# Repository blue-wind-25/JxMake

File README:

====================================================================================================
JxMake
====================================================================================================

JxMake is a Java-based cross-platform build system primarily inspired by the syntax and features of
GNU Make, Perforce Jam, and CMake.

Additionally, JxMake supports several features not typically found in other console-based build
systems, including a simple built-in GUI, a serial console, a serial plotter, and integrated
programmers for some commonly used MCUs. The JxMake repository also includes hardware schematics
and PCB designs ranging from simple to moderately complex, covering generic GPIO, basic programmers,
and various tools.

Building JxMake requires Java SDK 8 or later (note that Java SDK 8 is an LTS version).

This project is mirrored on both SourceForge and GitHub:
    https://sourceforge.net/projects/jxmake
    https://github.com/blue-wind-25/JxMake

----------------------------------------------------------------------------------------------------

Please refer to the JxMake usage page (run it with the '-h' or '--browse-docs' option) for how to
use the program.

Please refer to 'docs/*.txt', 'test/*.jxm', and 'test/src/*/JxMakeFile' for the scripting language
syntax and examples.

----------------------------------------------------------------------------------------------------

All preprocessed '*.java' files that generated from their corresponding '*.java.in' files (and
optionally some '*.java.inc' files) are preprocessed using PCPP ('3rd_party/tools/pcpp/pcmd.py')
and GNU sed.

Currently, JxMake's loadable libraries (build scripts) are primarily focused on embedded systems
development. Future updates will enhance support for building desktop applications. However, please
note that these libraries are quite basic, so you may prefer to create custom libraries tailored
to your projects.

----------------------------------------------------------------------------------------------------
----------------------------------------------------------------------------------------------------
----------------------------------------------------------------------------------------------------

If you like this software (or part of this software), please consider donating to:
    PayPal: aloysius.indrayanto@gmail.com
to support the software development.

====================================================================================================

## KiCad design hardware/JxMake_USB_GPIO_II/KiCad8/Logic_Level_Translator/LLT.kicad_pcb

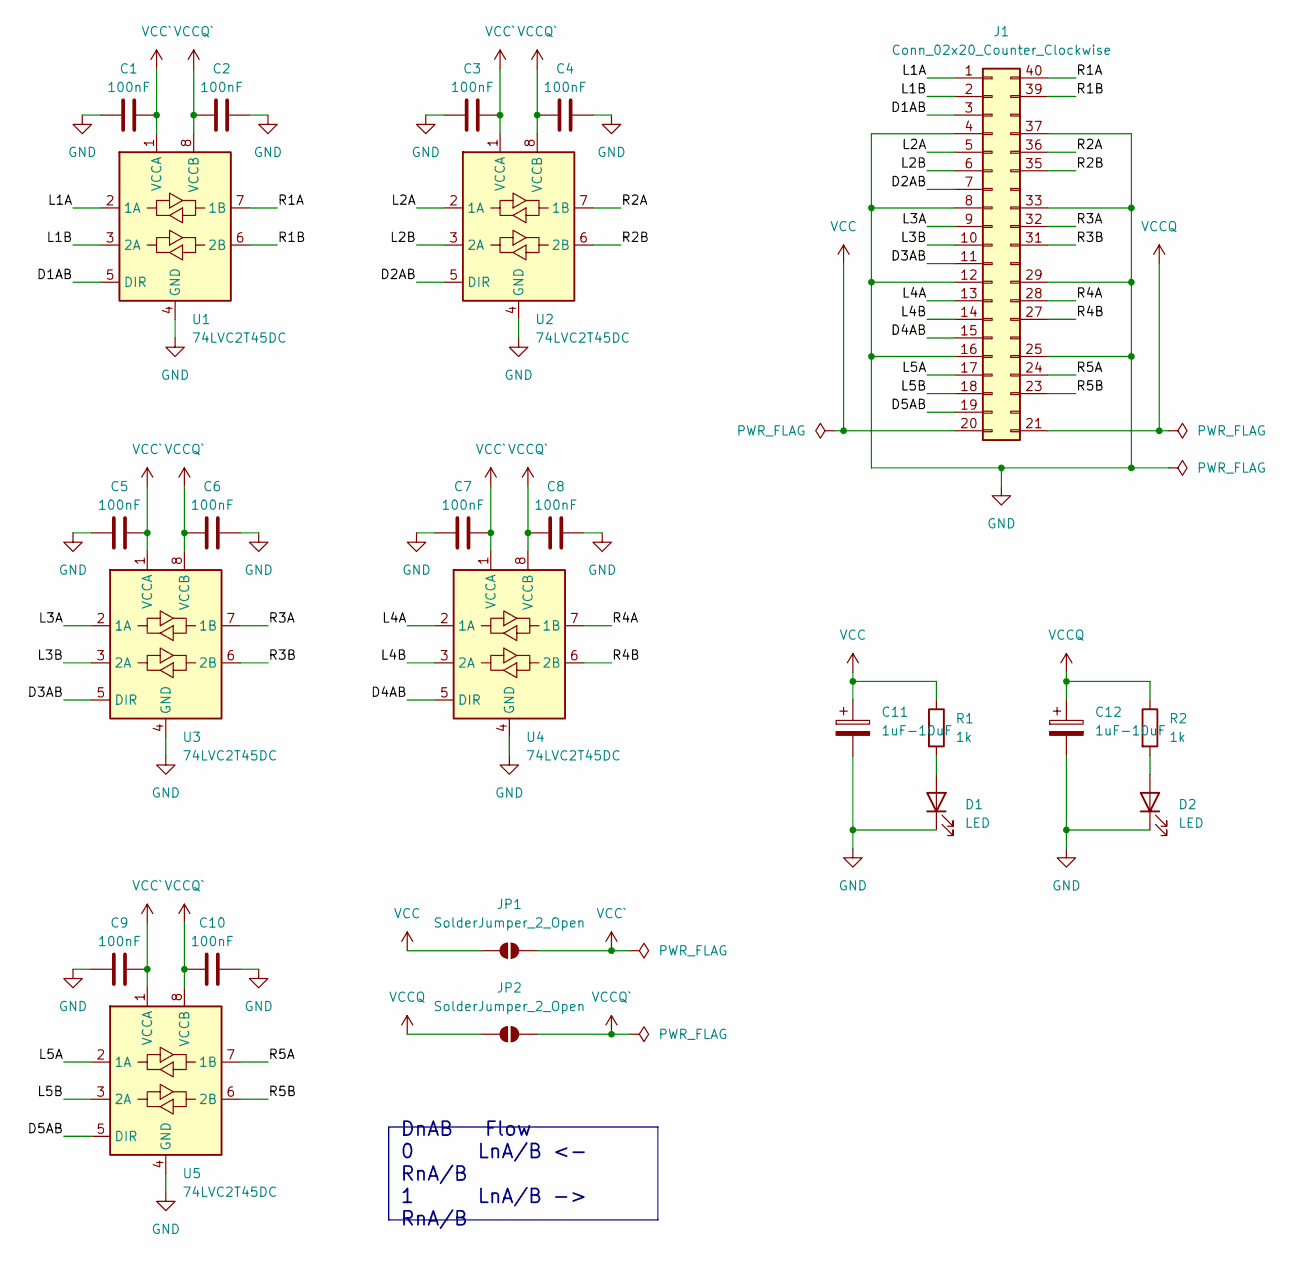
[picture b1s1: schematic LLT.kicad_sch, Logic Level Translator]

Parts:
C1, C2, C3, C4, C5, C6, C7, C8, C9, C10: 100nF; C_0805_2012Metric_Pad1.18x1.45mm_HandSolder
C11, C12: 1uF-10uF; CP_EIA-3216-12_Kemet-S_Pad1.58x1.35mm_HandSolder
D1, D2: LED; LED_0805_2012Metric_Pad1.15x1.40mm_HandSolder
J1: Conn_02x20_Counter_Clockwise; DIP-40_W25.4mm_LongPads
JP1, JP2: SolderJumper_2_Open; SolderJumper-2_P1.3mm_Open_Pad1.0x1.5mm
R1, R2: 1k; R_0805_2012Metric_Pad1.20x1.40mm_HandSolder
U1, U2, U3, U4, U5: 74LVC2T45DC; VSSOP-8_2.3x2mm_P0.5mm

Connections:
/D1AB: J1.3, U1.5 (DIR)
/D2AB: J1.7, U2.5 (DIR)
/D3AB: J1.11, U3.5 (DIR)
/D4AB: J1.15, U4.5 (DIR)
/D5AB: J1.19, U5.5 (DIR)
/L1A: J1.1, U1.2 (1A)
/L1B: J1.2, U1.3 (2A)
/L2A: J1.5, U2.2 (1A)
/L2B: J1.6, U2.3 (2A)
/L3A: J1.9, U3.2 (1A)
/L3B: J1.10, U3.3 (2A)
/L4A: J1.13, U4.2 (1A)
/L4B: J1.14, U4.3 (2A)
/L5A: J1.17, U5.2 (1A)
/L5B: J1.18, U5.3 (2A)
/R1A: J1.40, U1.7 (1B)
/R1B: J1.39, U1.6 (2B)
/R2A: J1.36, U2.7 (1B)
/R2B: J1.35, U2.6 (2B)
/R3A: J1.32, U3.7 (1B)
/R3B: J1.31, U3.6 (2B)
/R4A: J1.28, U4.7 (1B)
/R4B: J1.27, U4.6 (2B)
/R5A: J1.24, U5.7 (1B)
/R5B: J1.23, U5.6 (2B)
GND: C1.1, C2.2, C3.1, C4.2, C5.1, C6.2, C7.1, C8.2, C9.1, C10.2, C11.2, C12.2, D1.1 (K), D2.1 (K), J1.4, J1.8, J1.12, J1.16, J1.25, J1.29, J1.33, J1.37, U1.4 (GND), U2.4 (GND), U3.4 (GND), U4.4 (GND), U5.4 (GND)
unnamed: D1.2 (A), R1.2
unnamed: D2.2 (A), R2.2
VCC: C11.1, J1.20, JP1.1 (A), R1.1
VCCQ: C12.1, J1.21, JP2.1 (A), R2.1
VCCQ`: C2.1, C4.1, C6.1, C8.1, C10.1, JP2.2 (B), U1.8 (VCCB), U2.8 (VCCB), U3.8 (VCCB), U4.8 (VCCB), U5.8 (VCCB)
VCC`: C1.2, C3.2, C5.2, C7.2, C9.2, JP1.2 (B), U1.1 (VCCA), U2.1 (VCCA), U3.1 (VCCA), U4.1 (VCCA), U5.1 (VCCA)

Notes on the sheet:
DnAB Flow 0 LnA/B <- RnA/B 1 LnA/B -> RnA/B

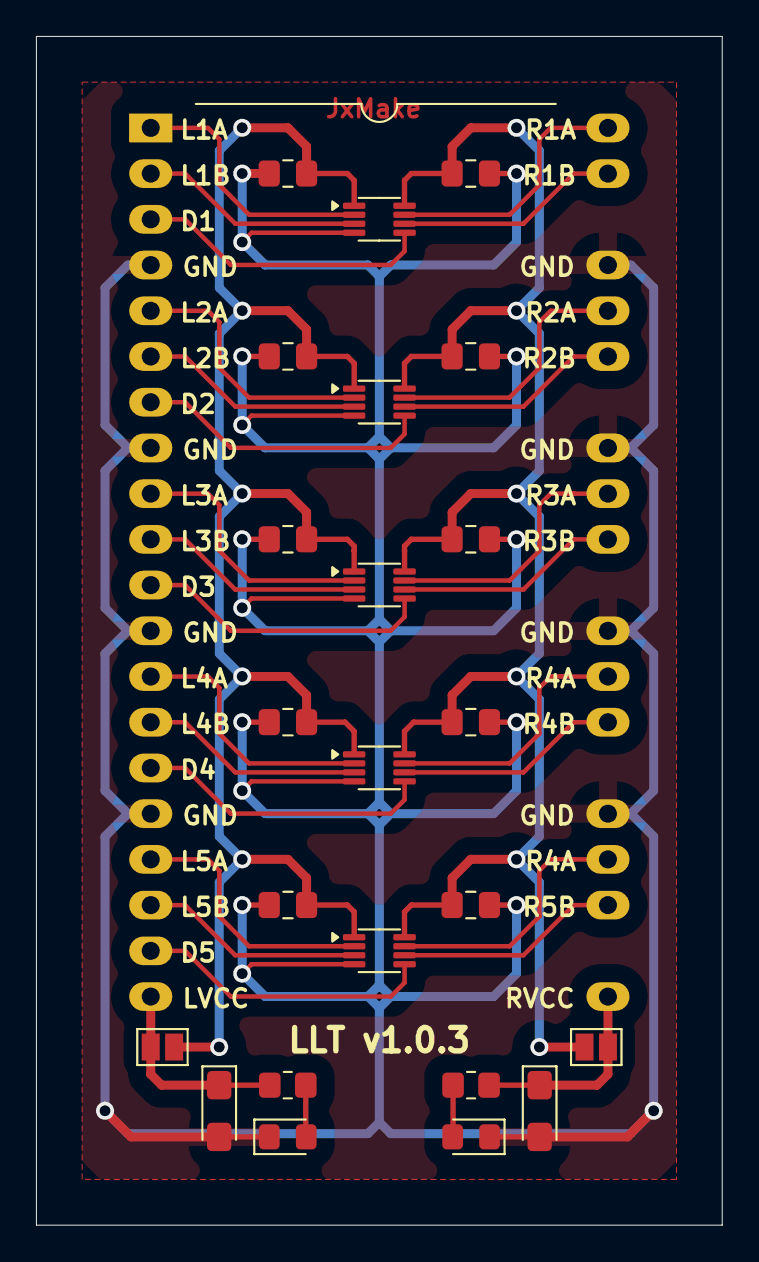
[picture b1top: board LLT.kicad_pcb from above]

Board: 2 copper layers, 38.1 x 66.0 mm, 24 parts (0 on the bottom side), 32 nets.

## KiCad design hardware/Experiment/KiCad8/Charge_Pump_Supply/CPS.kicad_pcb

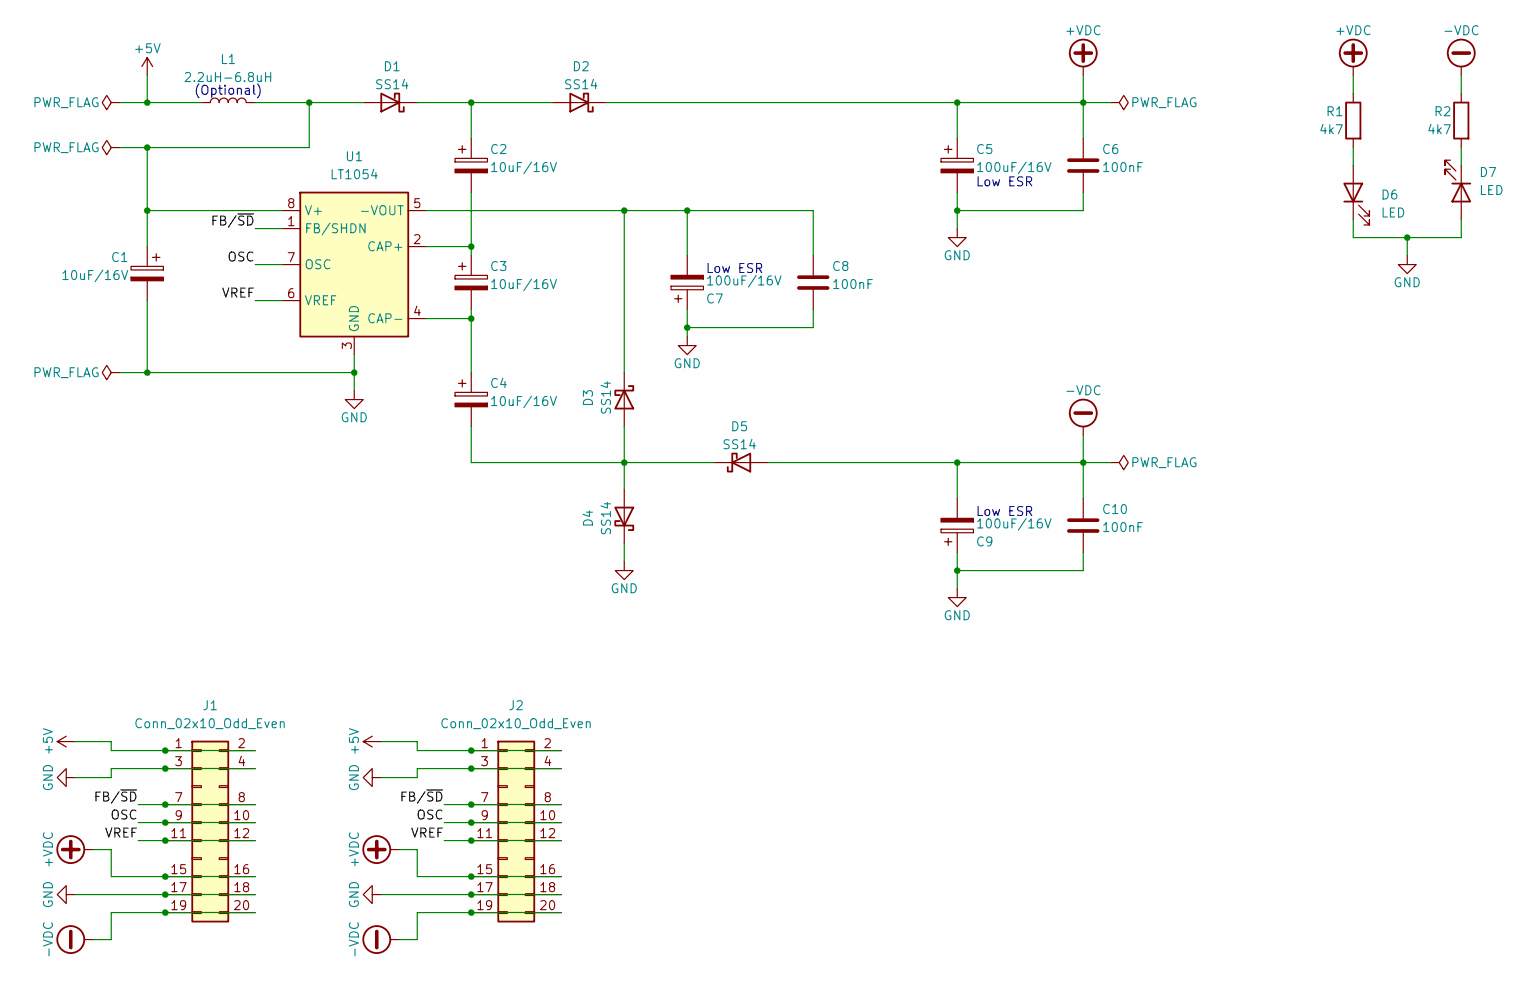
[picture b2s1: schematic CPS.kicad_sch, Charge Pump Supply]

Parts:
C1, C2, C3, C4: 10uF/16V; CP_EIA-3528-21_Kemet-B_Pad1.50x2.35mm_HandSolder
C5, C7, C9: 100uF/16V; CP_Elec_6.3x7.7
C6, C8, C10: 100nF; C_0805_2012Metric_Pad1.18x1.45mm_HandSolder
D1, D2, D3, D4, D5: SS14; D_SMA
D6, D7: LED; LED_0805_2012Metric_Pad1.15x1.40mm_HandSolder
J1, J2: Conn_02x10_Odd_Even; PinHeader_2x10_P2.54mm_Vertical
L1: 2.2uH-6.8uH; L_7.3x7.3_H4.5
R1, R2: 4k7; R_0805_2012Metric_Pad1.20x1.40mm_HandSolder
U1: LT1054; DIP-8_W7.62mm_LongPads

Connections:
+5V: J1.1, J1.2, J2.1, J2.2, L1.1
+VDC: C5.1, C6.1, D2.1 (K), J1.15, J1.16, J2.15, J2.16, R1.1
-VDC: C9.2, C10.1, D5.2 (A), J1.19, J1.20, J2.19, J2.20, R2.1
/FB/~SD: J1.7, J1.8, J2.7, J2.8, U1.1 (FB/SHDN)
/OSC: J1.9, J1.10, J2.9, J2.10, U1.7 (OSC)
/VREF: J1.11, J1.12, J2.11, J2.12, U1.6 (VREF)
GND: C1.2, C5.2, C6.2, C7.1, C8.2, C9.1, C10.2, D4.1 (K), D6.1 (K), D7.2 (A), J1.3, J1.4, J1.17, J1.18, J2.3, J2.4, J2.17, J2.18, U1.3 (GND)
unnamed: C1.1, D1.2 (A), L1.2, U1.8 (V+)
unnamed: C2.1, D1.1 (K), D2.2 (A)
unnamed: C4.2, D3.2 (A), D4.2 (A), D5.1 (K)
unnamed: C7.2, C8.1, D3.1 (K), U1.5 (-VOUT)
unnamed: D6.2 (A), R1.2
unnamed: D7.1 (K), R2.2
unnamed: C2.2, C3.1, U1.2 (CAP+)
unnamed: C3.2, C4.1, U1.4 (CAP-)

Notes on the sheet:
(Optional)
Low ESR

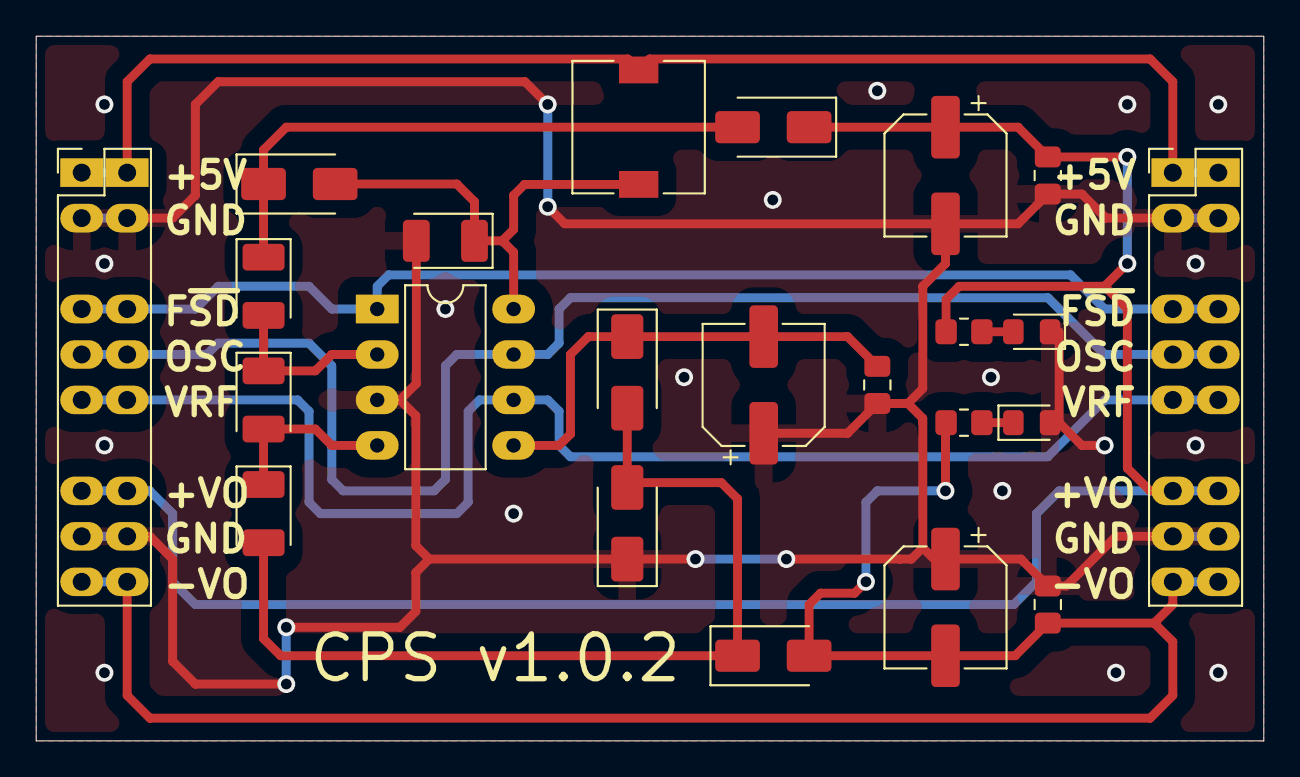
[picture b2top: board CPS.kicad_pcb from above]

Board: 2 copper layers, 68.6 x 39.4 mm, 23 parts (0 on the bottom side), 15 nets.

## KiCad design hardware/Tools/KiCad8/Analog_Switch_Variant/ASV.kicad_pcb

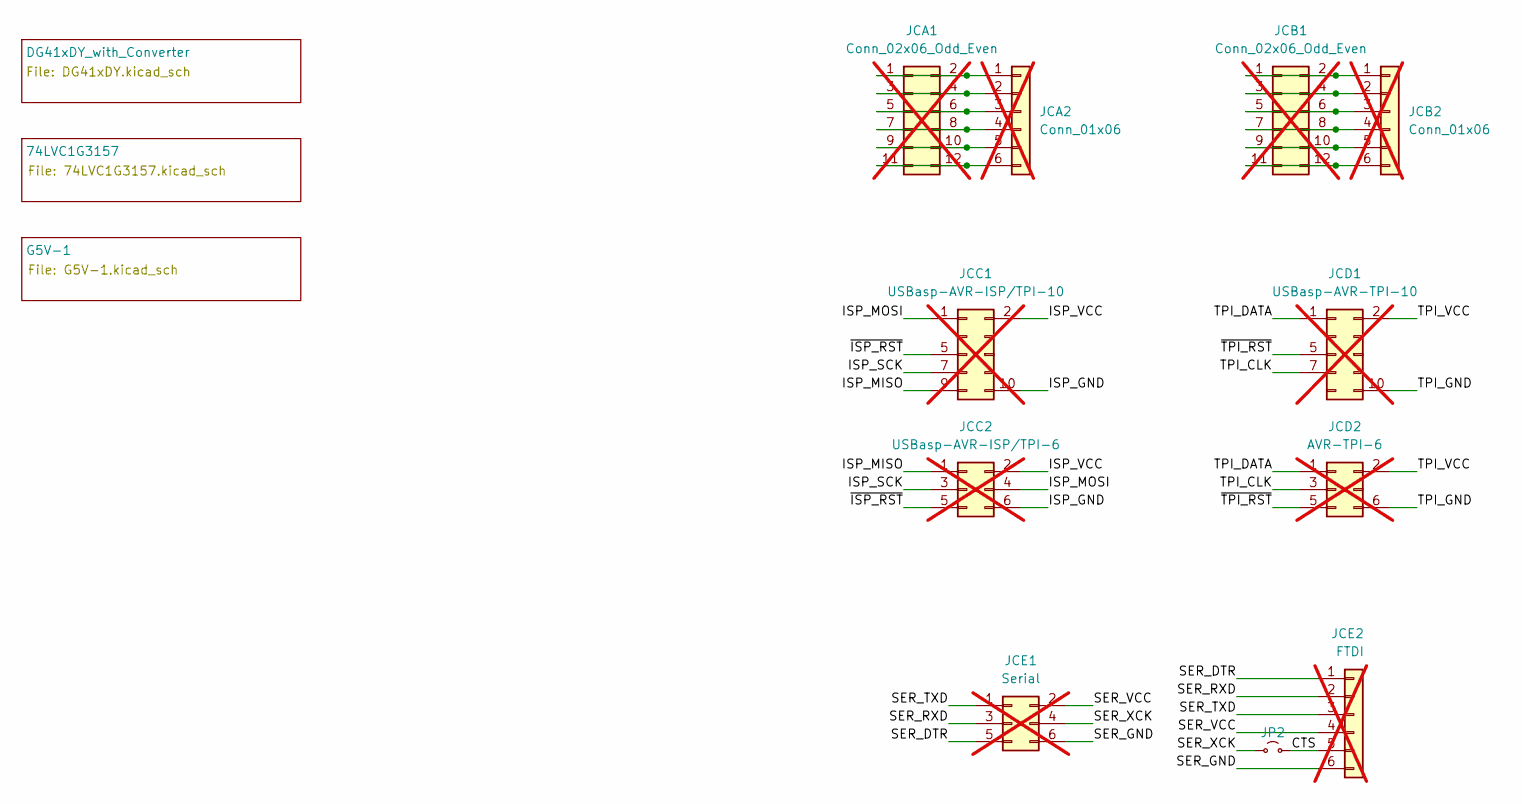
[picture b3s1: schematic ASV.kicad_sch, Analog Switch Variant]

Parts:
JCA1: Conn_02x06_Odd_Even; PinHeader_2x06_P2.54mm_Horizontal; not fitted
JCA2: Conn_01x06; PinHeader_1x06_P2.54mm_Horizontal; not fitted
JCB1: Conn_02x06_Odd_Even; PinHeader_2x06_P2.54mm_Horizontal; not fitted
JCB2: Conn_01x06; PinHeader_1x06_P2.54mm_Horizontal; not fitted
JCC1: USBasp-AVR-ISP/TPI-10; IDC-Header_2x05_P2.54mm_Vertical; not fitted
JCC2: USBasp-AVR-ISP/TPI-6; IDC-Header_2x03_P2.54mm_Vertical; not fitted
JCD1: USBasp-AVR-TPI-10; IDC-Header_2x05_P2.54mm_Vertical; not fitted
JCD2: AVR-TPI-6; IDC-Header_2x03_P2.54mm_Vertical; not fitted
JCE1: Serial; IDC-Header_2x03_P2.54mm_Vertical; not fitted
JCE2: FTDI; PinSocket_1x06_P2.54mm_Horizontal; not fitted
JP2: Jumper_2_Small_Open; SolderJumper-2_P1.3mm_Open_RoundedPad1.0x1.5mm

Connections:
/CTS: JCE2.5, JP2.2 (B)
/ISP_GND: JCC1.10, JCC2.6
/ISP_MISO: JCC1.9, JCC2.1
/ISP_MOSI: JCC1.1, JCC2.4
/ISP_SCK: JCC1.7, JCC2.3
/ISP_VCC: JCC1.2, JCC2.2
/SER_DTR: JCE1.5, JCE2.1
/SER_GND: JCE1.6, JCE2.6
/SER_RXD: JCE1.3, JCE2.2
/SER_TXD: JCE1.1, JCE2.3
/SER_VCC: JCE1.2, JCE2.4
/SER_XCK: JCE1.4, JP2.1 (A)
/TPI_CLK: JCD1.7, JCD2.3
/TPI_DATA: JCD1.1, JCD2.1
/TPI_GND: JCD1.10, JCD2.6
/TPI_VCC: JCD1.2, JCD2.2
/~ISP_RST: JCC1.5, JCC2.5
/~TPI_RST: JCD1.5, JCD2.5
unnamed: JCA1.1, JCA1.2, JCA2.1
unnamed: JCA1.3, JCA1.4, JCA2.2
unnamed: JCA1.5, JCA1.6, JCA2.3
unnamed: JCA1.7, JCA1.8, JCA2.4
unnamed: JCA1.9, JCA1.10, JCA2.5
unnamed: JCA1.11, JCA1.12, JCA2.6
unnamed: JCB1.1, JCB1.2, JCB2.1
unnamed: JCB1.3, JCB1.4, JCB2.2
unnamed: JCB1.5, JCB1.6, JCB2.3
unnamed: JCB1.7, JCB1.8, JCB2.4
unnamed: JCB1.9, JCB1.10, JCB2.5
unnamed: JCB1.11, JCB1.12, JCB2.6

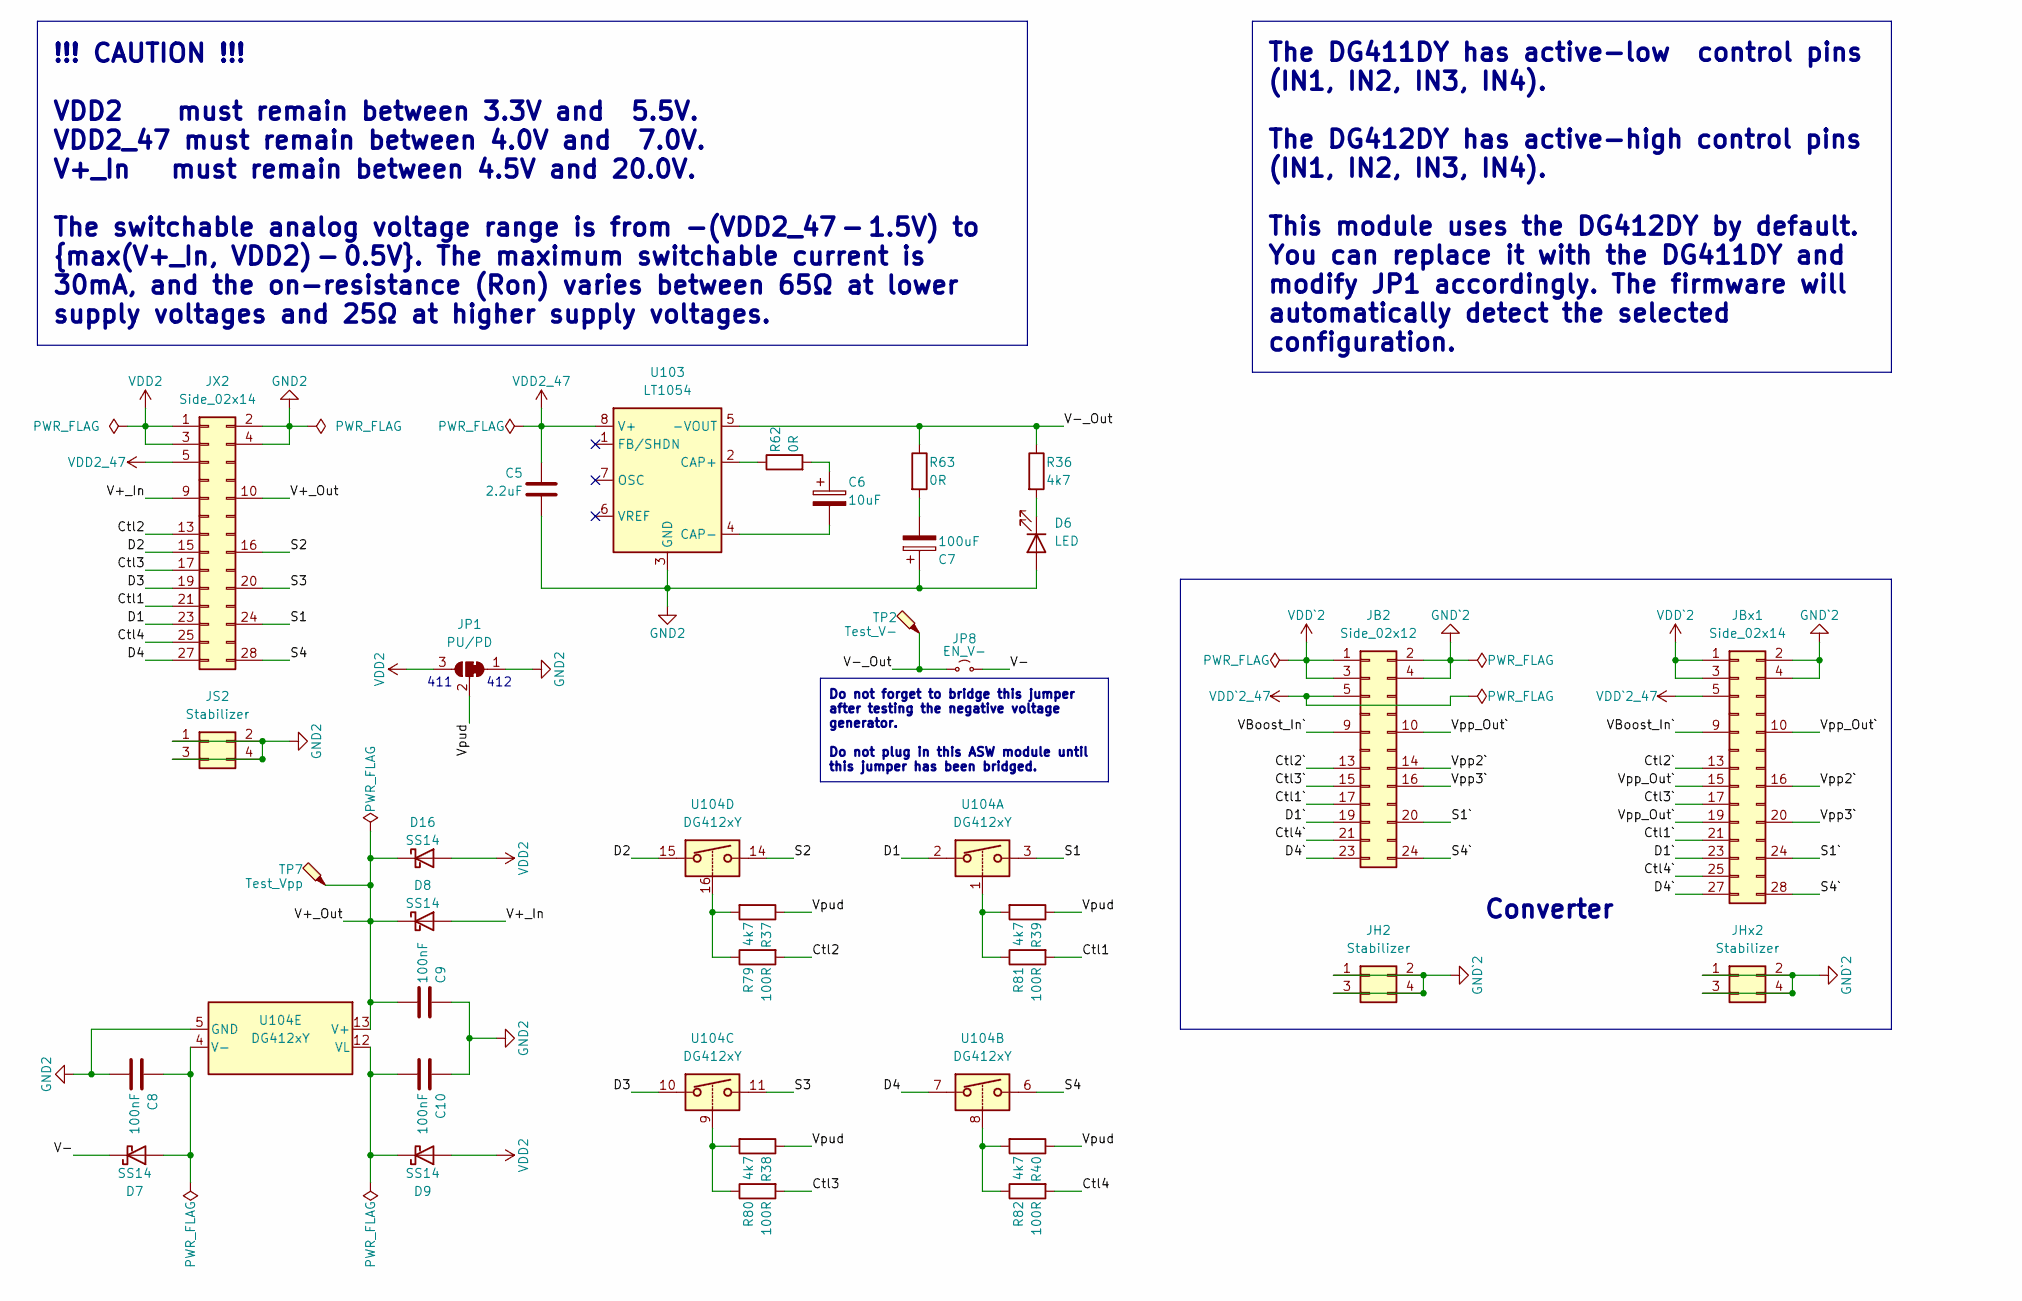
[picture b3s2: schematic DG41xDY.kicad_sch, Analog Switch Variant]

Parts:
C5: 2.2uF; C_0805_2012Metric_Pad1.18x1.45mm_HandSolder
C6: 10uF; CP_EIA-7360-38_Kemet-E_Pad2.25x4.25mm_HandSolder
C7: 100uF; CP_EIA-7360-38_Kemet-E_Pad2.25x4.25mm_HandSolder
C8, C9, C10: 100nF; C_0805_2012Metric_Pad1.18x1.45mm_HandSolder
D6: LED; LED_0805_2012Metric_Pad1.15x1.40mm_HandSolder
D7, D8, D9, D16: SS14; D_SMA
JB2: Side_02x12; PinHeader_2x12_P2.54mm_Vertical
JBx1: Side_02x14; PinHeader_2x14_P2.54mm_Vertical
JH2: Stabilizer; PinHeader_2x02_P2.54mm_Vertical
JHx2: Stabilizer; PinHeader_2x02_P2.54mm_Vertical
JP1: PU/PD; SolderJumper-3_P1.3mm_Bridged12_RoundedPad1.0x1.5mm
JP8: EN_V-; SolderJumper-2_P1.3mm_Open_RoundedPad1.0x1.5mm
JS2: Stabilizer; PinHeader_2x02_P2.54mm_Vertical
JX2: Side_02x14; PinHeader_2x14_P2.54mm_Vertical
R36, R37, R38, R39, R40: 4k7; R_0805_2012Metric_Pad1.20x1.40mm_HandSolder
R62, R63: 0R; R_0805_2012Metric_Pad1.20x1.40mm_HandSolder
R79, R80, R81, R82: 100R; R_0805_2012Metric_Pad1.20x1.40mm_HandSolder
TP2: Test_V-; TestPoint_THTPad_D1.5mm_Drill0.7mm
TP7: Test_Vpp; TestPoint_THTPad_D1.5mm_Drill0.7mm
U103: LT1054; DIP-8_W7.62mm_LongPads
U104: DG412xY; SOIC-16_3.9x9.9mm_P1.27mm

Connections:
/DG41xDY_with_Converter/Ctl1: JX2.21, R81.2
/DG41xDY_with_Converter/Ctl1`: JB2.17; also elsewhere on the board
/DG41xDY_with_Converter/Ctl2: JX2.13, R79.2
/DG41xDY_with_Converter/Ctl2`: JB2.13; also elsewhere on the board
/DG41xDY_with_Converter/Ctl3: JX2.17, R80.2
/DG41xDY_with_Converter/Ctl3`: JB2.15; also elsewhere on the board
/DG41xDY_with_Converter/Ctl4: JX2.25, R82.2
/DG41xDY_with_Converter/Ctl4`: JB2.21; also elsewhere on the board
/DG41xDY_with_Converter/D1: JX2.23, U104.2
/DG41xDY_with_Converter/D1`: JB2.19; also elsewhere on the board
/DG41xDY_with_Converter/D2: JX2.15, U104.15
/DG41xDY_with_Converter/D3: JX2.19, U104.10
/DG41xDY_with_Converter/D4: JX2.27, U104.7
/DG41xDY_with_Converter/D4`: JB2.23; also elsewhere on the board
/DG41xDY_with_Converter/S1: JX2.24, U104.3
/DG41xDY_with_Converter/S1`: JB2.20; also elsewhere on the board
/DG41xDY_with_Converter/S2: JX2.16, U104.14
/DG41xDY_with_Converter/S3: JX2.20, U104.11
/DG41xDY_with_Converter/S4: JX2.28, U104.6
/DG41xDY_with_Converter/S4`: JB2.24; also elsewhere on the board
/DG41xDY_with_Converter/V+_In: D8.2 (A), JX2.9
/DG41xDY_with_Converter/V+_Out: C9.2, D8.1 (K), D16.1 (K), JX2.10, TP7.1, U104.13 (V+)
/DG41xDY_with_Converter/V-: D7.1 (K), JP8.2 (B)
/DG41xDY_with_Converter/V-_Out: JP8.1 (A), R36.1, R63.1, TP2.1, U103.5 (-VOUT)
/DG41xDY_with_Converter/VBoost_In`: JB2.9; also elsewhere on the board
/DG41xDY_with_Converter/Vpp2`: JB2.14; also elsewhere on the board
/DG41xDY_with_Converter/Vpp3`: JB2.16; also elsewhere on the board
/DG41xDY_with_Converter/Vpp_Out`: JB2.10; also elsewhere on the board
/DG41xDY_with_Converter/Vpud: JP1.2 (C), R37.1, R38.1, R39.1, R40.1
GND2: C5.2, C7.1, C8.2, C9.1, C10.1, D6.2 (A), JP1.1 (A), JS2.1, JS2.2, JS2.3, JS2.4, JX2.2, JX2.4, U103.3 (GND), U104.5 (GND)
GND`2: JB2.2, JB2.4, JH2.1, JH2.2, JH2.3, JH2.4, JHx2.1, JHx2.2, JHx2.3, JHx2.4; also elsewhere on the board
unnamed: C6.1, R62.2
unnamed: C7.2, R63.2
unnamed: D6.1 (K), R36.2
unnamed: C8.1, D7.2 (A), U104.4 (V-)
unnamed: C10.2, D9.1 (K), U104.12 (VL)
unnamed: R37.2, R79.1, U104.16
unnamed: R38.2, R80.1, U104.9
unnamed: R39.2, R81.1, U104.1
unnamed: R40.2, R82.1, U104.8
unnamed: R62.1, U103.2 (CAP+)
unnamed: C6.2, U103.4 (CAP-)
VDD2: D9.2 (A), D16.2 (A), JP1.3 (B), JX2.1, JX2.3
VDD2_47: C5.1, JX2.5, U103.8 (V+)
VDD`2: JB2.1, JB2.3; also elsewhere on the board
VDD`2_47: JB2.5; also elsewhere on the board

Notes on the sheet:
Do not forget to bridge this jumper after testing the negative voltage generator. Do not plug in this ASW module until this jumper has been bridged.
The DG411DY has active-low control pins (IN1, IN2, IN3, IN4). The DG412DY has active-high control pins (IN1, IN2, IN3, IN4). This module uses the DG412DY by default. You can replace it with the DG411DY and modify JP1 accordingly. The firmware will automatically detect the selected configuration.
!!! CAUTION !!! VDD2 must remain between 3.3V and 5.5V. VDD2_47 must remain between 4.0V and 7.0V. V+_In must remain between 4.5V and 20.0V. The switchable analog voltage range is from -(VDD2_47 - 1.5V) to {max(V+_In, VDD2) - 0.5V}. The maximum switchable current is 30mA, and the on-resistance (Ron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
Converter
411
412

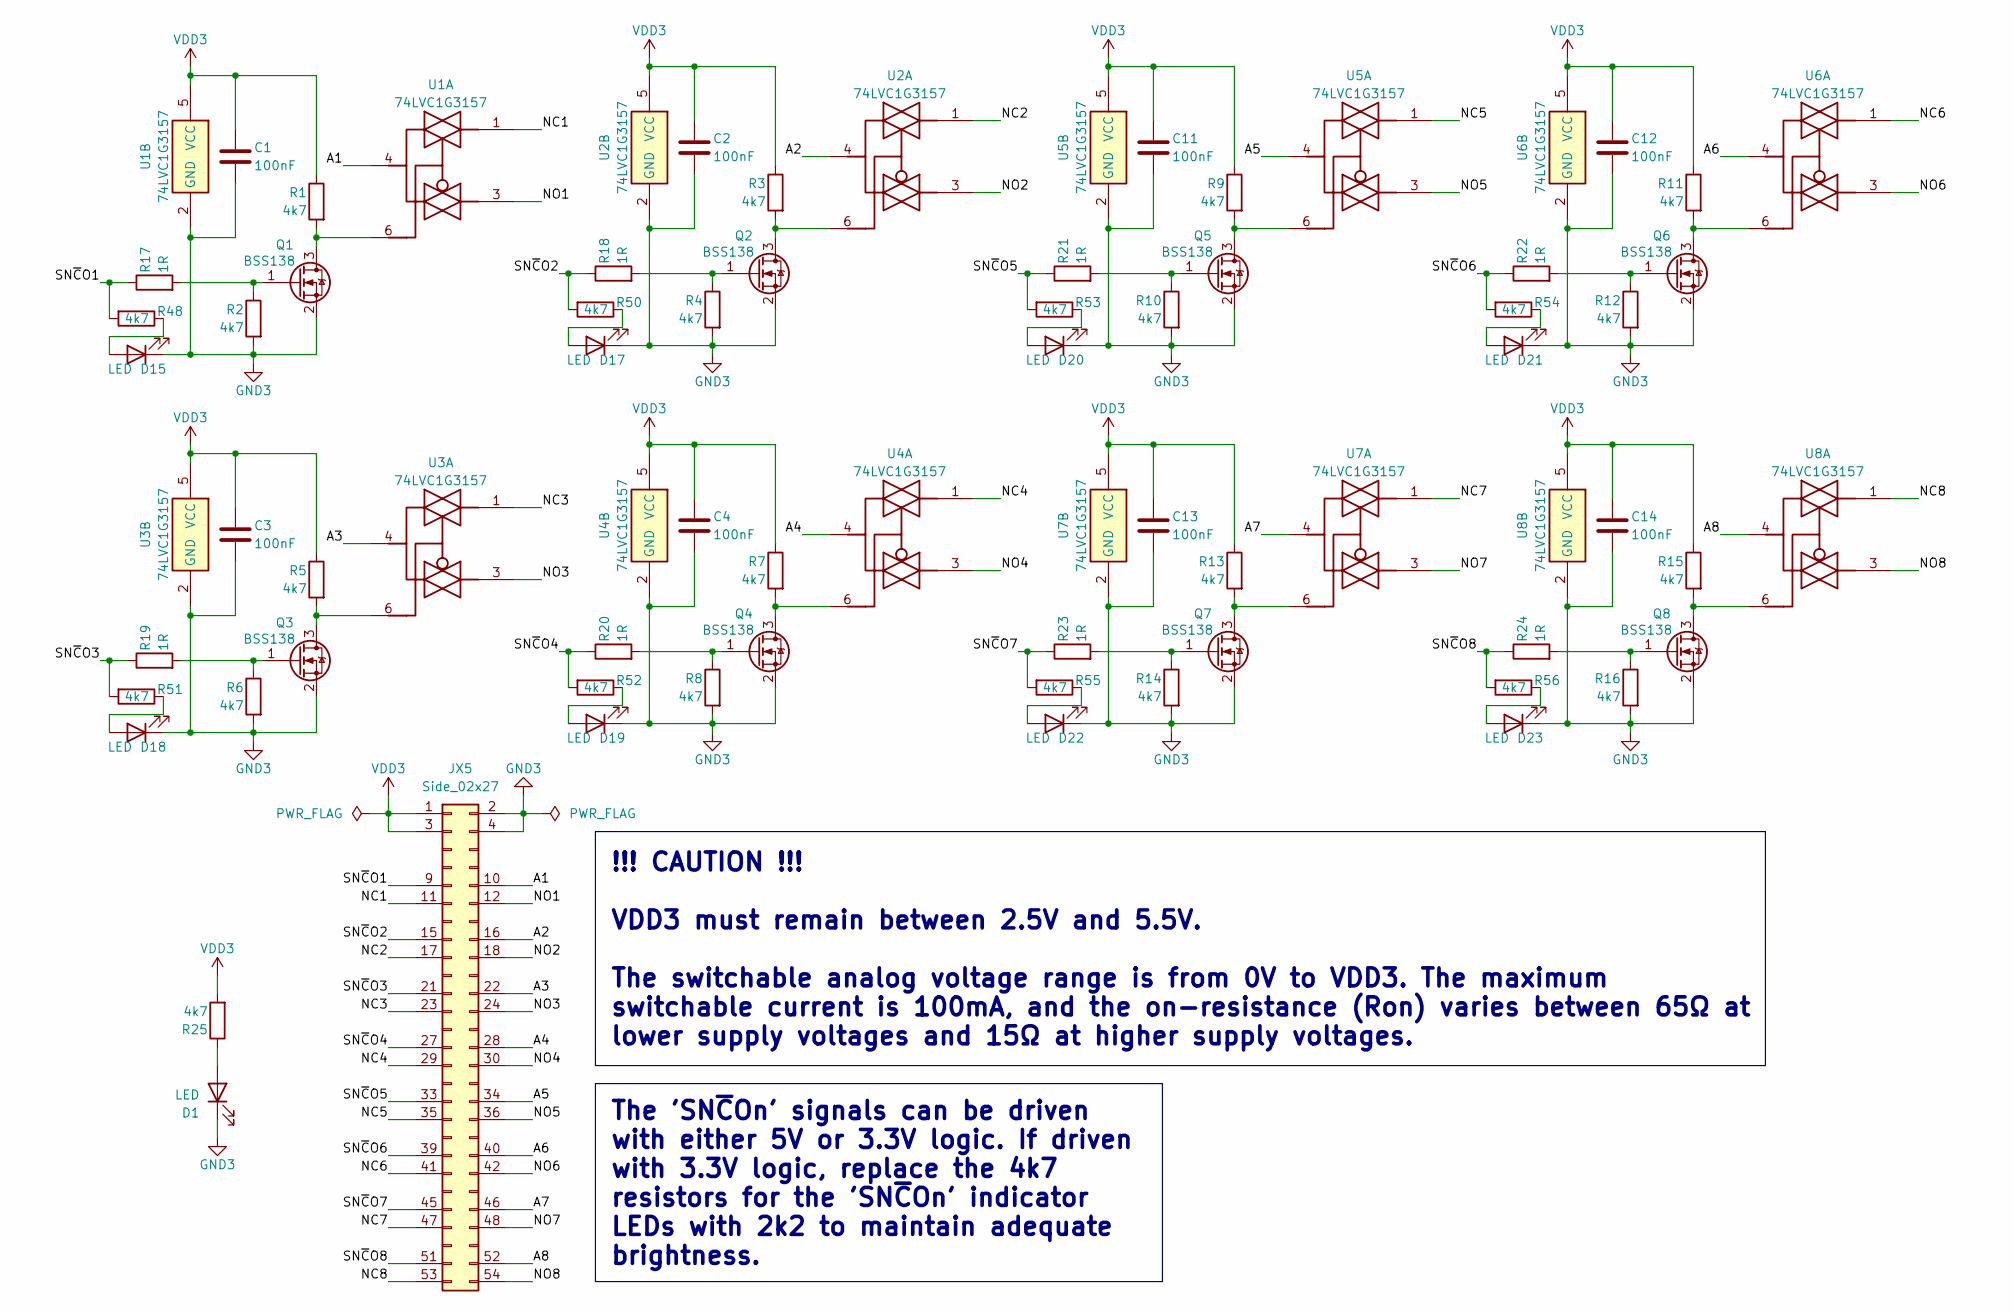
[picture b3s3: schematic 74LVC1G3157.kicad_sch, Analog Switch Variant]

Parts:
C1, C2, C3, C4, C11, C12, C13, C14: 100nF; C_0805_2012Metric_Pad1.18x1.45mm_HandSolder
D1, D15, D17, D18, D19, D20, D21, D22, D23: LED; LED_0805_2012Metric_Pad1.15x1.40mm_HandSolder
JX5: Side_02x27; PinHeader_2x27_P2.54mm_Vertical
Q1, Q2, Q3, Q4, Q5, Q6, Q7, Q8: BSS138; SOT-23_Handsoldering
R1, R2, R3, R4, R5, R6, R7, R8, R9, R10, R11, R12, R13, R14, R15, R16, R25, R48, R50, R51, R52, R53, R54, R55, R56: 4k7; R_0805_2012Metric_Pad1.20x1.40mm_HandSolder
R17, R18, R19, R20, R21, R22, R23, R24: 1R; R_0805_2012Metric_Pad1.20x1.40mm_HandSolder
U1, U2, U3, U4, U5, U6, U7, U8: 74LVC1G3157; SOT-23-6_Handsoldering

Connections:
/74LVC1G3157/A1: JX5.10, U1.4
/74LVC1G3157/A2: JX5.16, U2.4
/74LVC1G3157/A3: JX5.22, U3.4
/74LVC1G3157/A4: JX5.28, U4.4
/74LVC1G3157/A5: JX5.34, U5.4
/74LVC1G3157/A6: JX5.40, U6.4
/74LVC1G3157/A7: JX5.46, U7.4
/74LVC1G3157/A8: JX5.52, U8.4
/74LVC1G3157/NC1: JX5.11, U1.1
/74LVC1G3157/NC2: JX5.17, U2.1
/74LVC1G3157/NC3: JX5.23, U3.1
/74LVC1G3157/NC4: JX5.29, U4.1
/74LVC1G3157/NC5: JX5.35, U5.1
/74LVC1G3157/NC6: JX5.41, U6.1
/74LVC1G3157/NC7: JX5.47, U7.1
/74LVC1G3157/NC8: JX5.53, U8.1
/74LVC1G3157/NO1: JX5.12, U1.3
/74LVC1G3157/NO2: JX5.18, U2.3
/74LVC1G3157/NO3: JX5.24, U3.3
/74LVC1G3157/NO4: JX5.30, U4.3
/74LVC1G3157/NO5: JX5.36, U5.3
/74LVC1G3157/NO6: JX5.42, U6.3
/74LVC1G3157/NO7: JX5.48, U7.3
/74LVC1G3157/NO8: JX5.54, U8.3
/74LVC1G3157/SN~CO1: JX5.9, R17.1, R48.2
/74LVC1G3157/SN~CO2: JX5.15, R18.1, R50.2
/74LVC1G3157/SN~CO3: JX5.21, R19.1, R51.2
/74LVC1G3157/SN~CO4: JX5.27, R20.1, R52.2
/74LVC1G3157/SN~CO5: JX5.33, R21.1, R53.2
/74LVC1G3157/SN~CO6: JX5.39, R22.1, R54.2
/74LVC1G3157/SN~CO7: JX5.45, R23.1, R55.2
/74LVC1G3157/SN~CO8: JX5.51, R24.1, R56.2
GND3: C1.2, C2.2, C3.2, C4.2, C11.2, C12.2, C13.2, C14.2, D1.1 (K), D15.1 (K), D17.1 (K), D18.1 (K), D19.1 (K), D20.1 (K), D21.1 (K), D22.1 (K), D23.1 (K), JX5.2, JX5.4, Q1.2 (S), Q2.2 (S), Q3.2 (S), Q4.2 (S), Q5.2 (S), Q6.2 (S), Q7.2 (S), Q8.2 (S), R2.2, R4.2, R6.2, R8.2, R10.2, R12.2, R14.2, R16.2, U1.2 (GND), U2.2 (GND), U3.2 (GND), U4.2 (GND), U5.2 (GND), U6.2 (GND), U7.2 (GND), U8.2 (GND)
unnamed: D1.2 (A), R25.1
unnamed: D15.2 (A), R48.1
unnamed: D17.2 (A), R50.1
unnamed: D18.2 (A), R51.1
unnamed: D19.2 (A), R52.1
unnamed: D20.2 (A), R53.1
unnamed: D21.2 (A), R54.1
unnamed: D22.2 (A), R55.1
unnamed: D23.2 (A), R56.1
unnamed: Q1.3 (D), R1.2, U1.6
unnamed: Q1.1 (G), R2.1, R17.2
unnamed: Q2.3 (D), R3.2, U2.6
unnamed: Q2.1 (G), R4.1, R18.2
unnamed: Q3.3 (D), R5.2, U3.6
unnamed: Q3.1 (G), R6.1, R19.2
unnamed: Q4.3 (D), R7.2, U4.6
unnamed: Q4.1 (G), R8.1, R20.2
unnamed: Q5.3 (D), R9.2, U5.6
unnamed: Q5.1 (G), R10.1, R21.2
unnamed: Q6.3 (D), R11.2, U6.6
unnamed: Q6.1 (G), R12.1, R22.2
unnamed: Q7.3 (D), R13.2, U7.6
unnamed: Q7.1 (G), R14.1, R23.2
unnamed: Q8.3 (D), R15.2, U8.6
unnamed: Q8.1 (G), R16.1, R24.2
VDD3: C1.1, C2.1, C3.1, C4.1, C11.1, C12.1, C13.1, C14.1, JX5.1, JX5.3, R1.1, R3.1, R5.1, R7.1, R9.1, R11.1, R13.1, R15.1, R25.2, U1.5 (VCC), U2.5 (VCC), U3.5 (VCC), U4.5 (VCC), U5.5 (VCC), U6.5 (VCC), U7.5 (VCC), U8.5 (VCC)

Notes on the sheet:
!!! CAUTION !!! VDD3 must remain between 2.5V and 5.5V. The switchable analog voltage range is from 0V to VDD3. The maximum switchable current is 100mA, and the on-resistance (Ron) varies between 65Ω at lower supply voltages and 15Ω at higher supply voltages.
The 'SN~{C}On' signals can be driven with either 5V or 3.3V logic. If driven with 3.3V logic, replace the 4k7 resistors for the 'SN~{C}On' indicator LEDs with 2k2 to maintain adequate brightness.

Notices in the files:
README:
License: LGPL v3+
hardware/Experiment/KiCad8/Charge_Pump_Supply/CPS.kicad_pcb:
Copyright (C) Aloysius Indrayanto
